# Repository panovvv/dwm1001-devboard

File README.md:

# DWM1001 Development board
Breakout board for DWM1001 UWB module.

[> Demo video here <](https://www.youtube.com/watch?v=SorOhWdywFg)

Intended for easy exploration:
* Modular thanks to compatibility with Arduino Uno shield footprint.
* Modules can be battery-powered using a simple DIY battery shield.
* Open access to all GPIOs.

## Files and folders:

* `dwm1001-devboard.***`- KiCAD schematics and PCB files.
* `schematic.pdf` - full schematic sheet rendered in PDF.
* `bom.csv` - Bill of Materials, semicolon-separated.
* `paper_footprint_test.pdf` - this is my usual practice when designing and ordering PCBs:
before even designing the board layout, I plot the empty board with all footprints in it to PDF
(1:1 scale), print it on a sheet of paper and do a "test fit" for every component. This helps 
to find footprint inconsistencies early on.
* `gerber/` - Generated according to
[this document](https://support.jlcpcb.com/article/102-kicad-515---generating-gerber-and-drill-files).
To order the PCB made, just zip up all files in `gerber/` folder and send to fab.
* `renders/` - 3D renders and STL of the board with all components populated.
* `SMD_Polyfuse_1812.stp` - model for PTC fuse in 1812 package, courtesy of 
  [Joan The Spark](https://forum.kicad.info/u/Joan_Sparky) distributed under GNU General Public License v2.0. 
  Source: [Kicad forum](https://forum.kicad.info/t/polyfuse-3d-models/6859), [direct link](https://kicad-info.s3-us-west-2.amazonaws.com/original/2X/6/6d10c55baa8ffbd4a3f9c269ba751e2fab07bd70.stp)

## BOM

|Designator|Package                                     |Quantity|Value                                |
|----------|--------------------------------------------|--------|-------------------------------------|
|F2,F1     |1812 (4532 Metric)                          |2       |0.5A PTC fuse                        |
|C2,C1     |0603 (1608 Metric)                          |2       |22pF ceramic capacitor               |
|Y1        |HC49-SD SMD                                 |1       |12MHz crystal oscillator             |
|U1        |SOIC-16                                     |1       |CH340G                               |
|J1        |Micro USB Type B, SMD                       |1       |Micro USB B connector, female        |
|SW1, SW2  |SPST Pushbutton 6x6mm, SMD                  |2       |WKUP, RST buttons                    |
|U3        |SOT-223-3                                   |1       |AMS1117-3.3 3.3V voltage regulator   |
|U2        |DecaWave DWM1001                            |1       |DWM1001                              |
|R1        |0805 (2012 Metric)                          |1       |100kΩ resistor                       |
|Q2,Q1     |SuperSOT-3                                  |2       |FDN430P P-MOSFET                     |
|JP1       |2.54mm pitch Male Pin Header 1x02 Vertical  |1       |3.3V Current probe jumper            |
|J7        |2.54mm pitch Female Pin Header 1x10 Vertical|1       |Arduino Stackable type if possible   |
|J6        |2.54mm pitch Female Pin Header 1x08 Vertical|1       |Arduino Stackable type if possible   |
|J4        |2.54mm pitch Female Pin Header 1x15 Vertical|1       |Arduino Stackable type if possible   |
|J5        |Tag-Connect TC2030-IDC                      |1       |Tag-Connect TC2030 SWD               |
|J2        |2.54mm pitch Male Pin Header 1x04 Vertical  |1       |SWD Pin Header Male                  |
|D4        |SMA or SMB Diode                            |1       |SMBJ3.3A Transient voltage suppressor|
|D1 - D3   |SMA or SMB Diode                            |3       |SMBJ5.0A Transient voltage suppressor|
|C5,C3     |0805 (2012 Metric)                          |2       |100nF ceramic capacitor              |
|C7,C6,C4  |0805 (2012 Metric)                          |3       |10µF ceramic capacitor               |
|D9        |0603 (1608 Metric)                          |1       |Green LED                            |
|D8,D6     |0603 (1608 Metric)                          |2       |Red LED                              |
|D7,D5     |0603 (1608 Metric)                          |2       |Blue LED                             |
|R6        |0805 (2012 Metric)                          |1       |47Ω resistor, for green LED @ 3.3V   |
|R5,R3     |0805 (2012 Metric)                          |2       |75Ω resistor, for red LED @ 3.3V     |
|R4,R2     |0805 (2012 Metric)                          |2       |15Ω resistor, for blue LED @ 3.3V    |

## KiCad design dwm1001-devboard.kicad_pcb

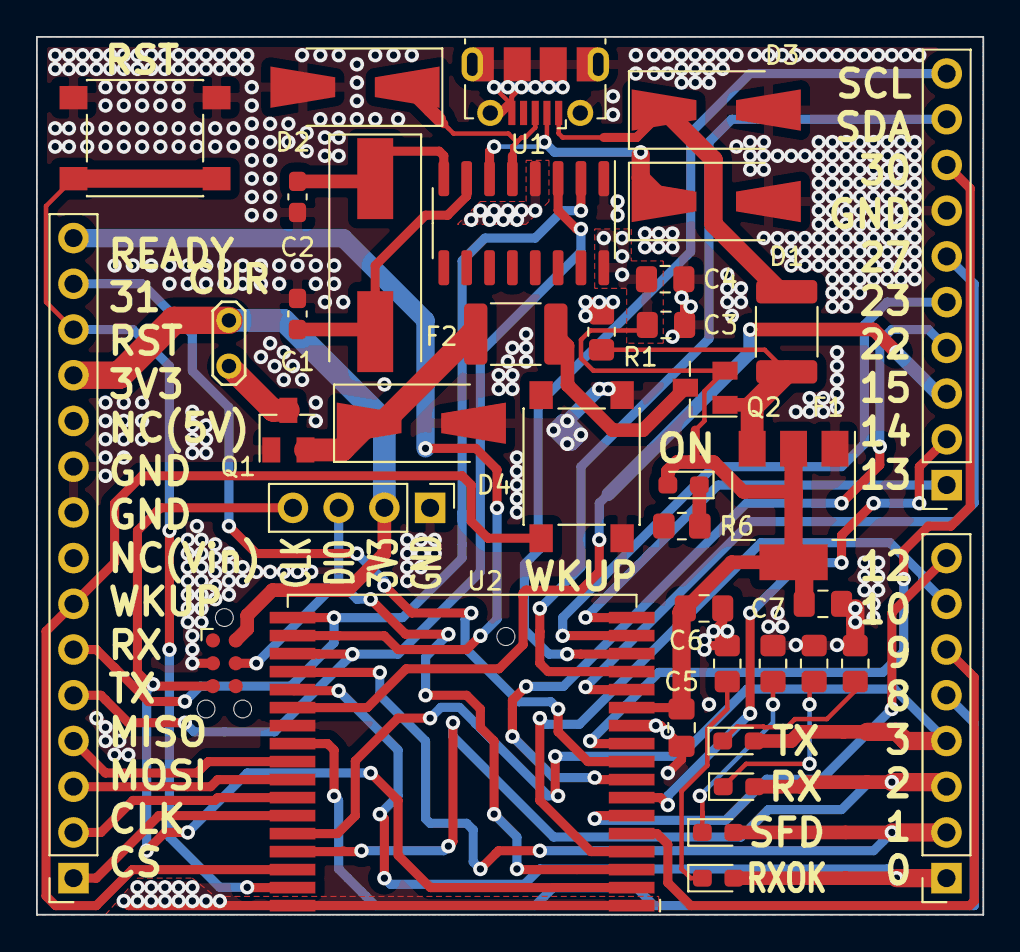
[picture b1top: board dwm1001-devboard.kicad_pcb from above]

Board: 2 copper layers, 52.6 x 48.8 mm, 39 parts (0 on the bottom side), 46 nets.

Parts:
C1, C2: 22p; C_0603_1608Metric_Pad1.08x0.95mm_HandSolder
C3, C5: 100n; C_0805_2012Metric_Pad1.18x1.45mm_HandSolder
C4, C6, C7: 10u; C_0805_2012Metric_Pad1.18x1.45mm_HandSolder
D1, D2, D3: SMBJ5.0A; D_SMA-SMB_Universal_Handsoldering
D4: SMBJ3.3A; D_SMA-SMB_Universal_Handsoldering
D5, D7: Blue; LED_0603_1608Metric_Pad1.05x0.95mm_HandSolder
D6, D8: Red; LED_0603_1608Metric_Pad1.05x0.95mm_HandSolder
D9: Green; LED_0603_1608Metric_Pad1.05x0.95mm_HandSolder
F1, F2: 0.5A PTC; Fuse_1812_4532Metric_Pad1.30x3.40mm_HandSolder
J1: Micro USB B; USB_Micro-B_Molex-105017-0001
J2: SWD Pin Header Male; PinHeader_1x04_P2.54mm_Vertical
J4: 15; PinSocket_1x15_P2.54mm_Vertical
J5: Tag-Connect TC2030 SWD; Tag-Connect_TC2030-IDC-NL_2x03_P1.27mm_Vertical
J6: 8; PinSocket_1x08_P2.54mm_Vertical
J7: 10; PinSocket_1x10_P2.54mm_Vertical
JP1: 3.3V Current probe; TestPoint_2Pads_Pitch2.54mm_Drill0.8mm
Q1, Q2: FDN430P; SuperSOT-3
R1: 100k; R_0805_2012Metric_Pad1.20x1.40mm_HandSolder
R2, R4: 15; R_0805_2012Metric_Pad1.20x1.40mm_HandSolder
R3, R5: 75; R_0805_2012Metric_Pad1.20x1.40mm_HandSolder
R6: 47; R_0805_2012Metric_Pad1.20x1.40mm_HandSolder
SW1: RST; SW_Push_1P1T_NO_6x6mm_H9.5mm
SW2: WKUP; SW_Push_1P1T_NO_6x6mm_H9.5mm
U1: CH340G; SOIC-16_3.9x9.9mm_P1.27mm
U2: DWM1001; DecaWave_DWM1001
U3: AMS1117-3.3; SOT-223-3_TabPin2
Y1: 12MHz; Crystal_SMD_HC49-SD

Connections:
+3V3: C3.1, C4.1, C5.1, C6.1, C7.1, D9.2, Q2.2, U1.4, U1.16, U2.12, U3.2
+5V: F1.1, Q2.1, R1.1, U3.3
/3.3V_IN: J2.2, J4.12, J5.2, JP1.1
/31: J4.14, U2.9
/DWM_RX: J4.6, U1.2, U2.18
/DWM_TX: J4.5, U1.3, U2.20
/GPIO0: D5.2, J6.1, U2.22
/GPIO1: D6.2, J6.2, U2.21
/GPIO2: D7.2, J6.3, U2.31
/GPIO3: D8.2, J6.4, U2.30
/READY: J4.15, U2.19
/RST: J4.13, SW1.2, U2.33
/SCL: J7.10, U2.15
/SDA: J7.9, U2.14
/SWDCLK: J2.4, J5.5, U2.2
/SWDIO: J2.3, J5.4, U2.3
/WKUP: J4.7, SW2.2, U2.32
GND: C1.2, C2.2, C3.2, C4.2, C5.2, C6.2, C7.2, D1.2, D2.2, D3.2, D4.2, J1.5, J1.6, J2.1, J4.9, J4.10, J5.3, J7.7, Q1.1, R1.2, R2.1, R3.1, R4.1, R5.1, R6.2, SW1.1, SW2.1, U1.1, U2.1, U2.11, U2.24, U2.34, U3.1
unnamed: C1.1, U1.7, Y1.2
unnamed: C2.1, U1.8, Y1.1
unnamed: D1.1, J1.2, U1.6
unnamed: D2.1, J1.3, U1.5
unnamed: D3.1, F1.2, J1.1
unnamed: D4.1, F2.2, Q1.2
unnamed: D5.1, R2.2
unnamed: D6.1, R3.2
unnamed: D7.1, R4.2
unnamed: D8.1, R5.2
unnamed: D9.1, R6.1
unnamed: F2.1, Q2.3
unnamed: J4.1, U2.29
unnamed: J4.2, U2.28
unnamed: J4.3, U2.27
unnamed: J4.4, U2.26
unnamed: J6.5, U2.25
unnamed: J6.6, U2.5
unnamed: J6.7, U2.4
unnamed: J6.8, U2.6
unnamed: J7.1, U2.17
unnamed: J7.2, U2.7
unnamed: J7.3, U2.23
unnamed: J7.4, U2.8
unnamed: J7.5, U2.16
unnamed: J7.6, U2.13
unnamed: J7.8, U2.10
unnamed: JP1.2, Q1.3

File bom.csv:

Designator;Package;Quantity;Value
F2,F1;Fuse 1812 (4532 Metric);2;0.5A PTC
C2,C1;Capacitor 0603 (1608 Metric);2;22p
Y1;HC49-SD SMD Crystal Oscillator;1;12MHz
U1;SOIC-16;1;CH340G
J1;Micro USB Type B, SMD;1;Micro USB B
SW1, SW2;SPST Pushbutton 6x6mm, SMD;2;WKUP, RST
U3;SOT-223-3;1;AMS1117-3.3
U2;DecaWave DWM1001;1;DWM1001
R1;Resistor 0805 (2012 Metric);1;100k
Q2,Q1;SuperSOT-3;2;FDN430P
JP1;2.54mm pitch Male Pin Header 1x02 Vertical;1;3.3V Current probe
J7;2.54mm pitch Female Pin Header 1x10 Vertical;1;Arduino Stackable type if possible
J6;2.54mm pitch Female Pin Header 1x08 Vertical;1;Arduino Stackable type if possible
J4;2.54mm pitch Female Pin Header 1x15 Vertical;1;Arduino Stackable type if possible
J5;Tag-Connect TC2030-IDC;1;Tag-Connect TC2030 SWD
J2;2.54mm pitch Male Pin Header 1x04 Vertical;1;SWD Pin Header Male
D4;SMA or SMB Diode;1;SMBJ3.3A
D1 - D3;SMA or SMB Diode;3;SMBJ5.0A
C5,C3;Capacitor 0805 (2012 Metric);2;100n
C7,C6,C4;Capacitor 0805 (2012 Metric);3;10u
D9;LED 0603 (1608 Metric);1;Green
D8,D6;LED 0603 (1608 Metric);2;Red
D7,D5;LED 0603 (1608 Metric);2;Blue
R6;Resistor 0805 (2012 Metric);1;47 Ohm, for green LED @ 3.3V
R5,R3;Resistor 0805 (2012 Metric);2;75 Ohm, for red LED @ 3.3V
R4,R2;Resistor 0805 (2012 Metric);2;15 Ohm, for blue LED @ 3.3V

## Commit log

2021-03-23 first implementation
2021-03-28 get rid of solder jumpers
2021-03-28 rename render, fix README.md
2021-03-31 remove solder jumpers, add dimensions to the PCB. First batch of PCBs ordered
2021-05-11 declutter BOM file
2021-09-27 small bom fix
2022-01-21 include video link
